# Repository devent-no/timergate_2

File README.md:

# timergate
PCB, 3D models, Firmware and software for timergates.

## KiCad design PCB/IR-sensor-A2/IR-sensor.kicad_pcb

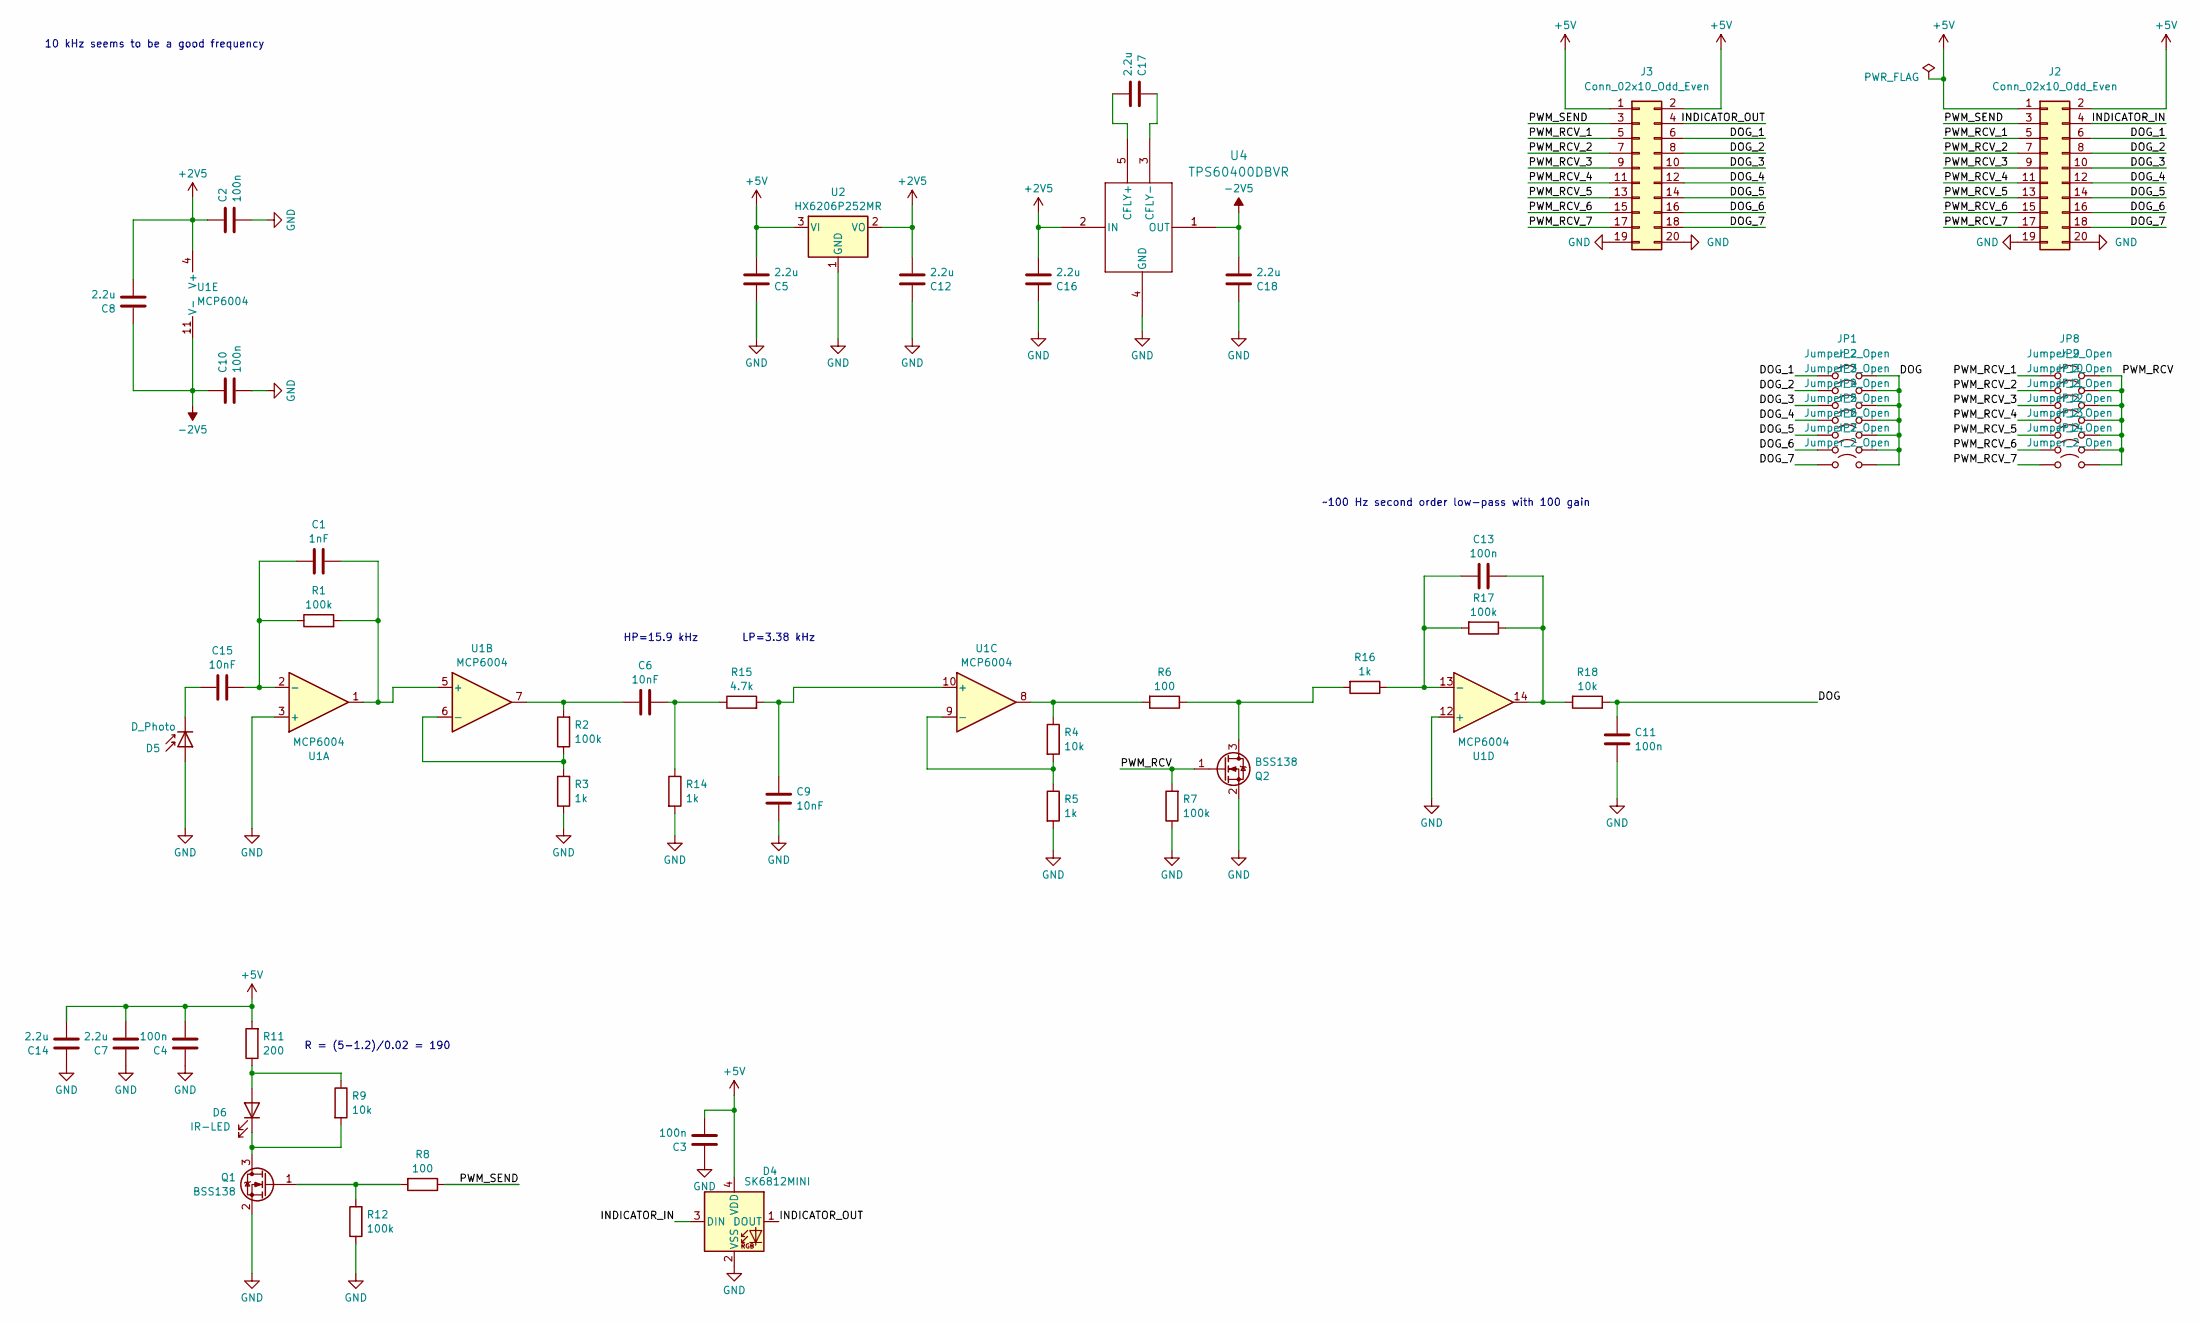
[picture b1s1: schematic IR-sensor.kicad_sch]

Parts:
C1: 1nF; C_0402_1005Metric; MPN CC0402KRX7R9BB102
C2, C3, C4, C10, C11, C13: 100n; C_0402_1005Metric; MPN CC0402KRX5R9BB104
C5, C7, C8, C12, C14, C16, C17, C18: 2.2u; C_0402_1005Metric; MPN CL05A225MQ5NSNC
C6, C9, C15: 10nF; C_0402_1005Metric; MPN CC0402KRX7R7BB103
D4: SK6812MINI; LED_SK6812MINI_PLCC4_3.5x3.5mm_P1.75mm; MPN SK6812mini
D5: D_Photo; LED_D5.0mm; MPN 1540051EC3590
D6: IR-LED; LED_D5.0mm; MPN VSLY5940
J2: Conn_02x10_Odd_Even; PinHeader_2x10_P1.27mm_Horizontal; MPN IPCP127M20PB28R
J3: Conn_02x10_Odd_Even; PinSocket_2x10_P1.27mm_Horizontal; MPN IPCP127F20PB28R
JP1, JP2, JP3, JP4, JP5, JP6, JP7, JP8, JP9, JP10, JP11, JP12, JP13, JP14: Jumper_2_Open; SolderJumper-2_P1.3mm_Open_Pad1.0x1.5mm
Q1, Q2: BSS138; SOT-23; MPN 4530-BSS138CT-ND
R1, R2, R7, R12, R17: 100k; R_0402_1005Metric; MPN RC0402FR-07100KL
R3, R5, R14, R16: 1k; R_0402_1005Metric; MPN 0402WGF1001TCE
R4, R9, R18: 10k; R_0402_1005Metric; MPN RC0402FR-0710KL
R6, R8: 100; R_0402_1005Metric; MPN RC0402FR-07100RL
R11: 200; R_0402_1005Metric; MPN 0402WGF2000TCE
R15: 4.7k; R_0402_1005Metric; MPN RC0402FR-074K7L
U1: MCP6004; SOIC-14_3.9x8.7mm_P1.27mm; MPN MCP6004T-I/SL
U2: HX6206P252MR; SOT-23-3; MPN HX6206P252MR
U4: TPS60400DBVR; SOT-23-5; MPN TPS60400DBVR

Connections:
+2V5: C2.2, C8.1, C12.2, C16.2, U1.4 (V+), U2.2 (VO), U4.2 (IN)
+5V: C3.1, C4.1, C5.2, C7.1, C14.1, D4.4 (VDD), J2.1, J2.2, J3.1, J3.2, R11.2, U2.3 (VI)
-2V5: C8.2, C10.2, C18.2, U1.11 (V-), U4.1 (OUT)
/DOG: C11.1, JP1.2 (B), JP2.2 (B), JP3.2 (B), JP4.2 (B), JP5.2 (B), JP6.2 (B), JP7.2 (B), R18.1
/DOG_1: J2.6, J3.6, JP1.1 (A)
/DOG_2: J2.8, J3.8, JP2.1 (A)
/DOG_3: J2.10, J3.10, JP3.1 (A)
/DOG_4: J2.12, J3.12, JP4.1 (A)
/DOG_5: J2.14, J3.14, JP5.1 (A)
/DOG_6: J2.16, J3.16, JP6.1 (A)
/DOG_7: J2.18, J3.18, JP7.1 (A)
/INDICATOR_IN: D4.3 (DIN), J2.4
/INDICATOR_OUT: D4.1 (DOUT), J3.4
/PWM_RCV: JP8.2 (B), JP9.2 (B), JP10.2 (B), JP11.2 (B), JP12.2 (B), JP13.2 (B), JP14.2 (B), Q2.1 (G), R7.2
/PWM_RCV_1: J2.5, J3.5, JP8.1 (A)
/PWM_RCV_2: J2.7, J3.7, JP9.1 (A)
/PWM_RCV_3: J2.9, J3.9, JP10.1 (A)
/PWM_RCV_4: J2.11, J3.11, JP11.1 (A)
/PWM_RCV_5: J2.13, J3.13, JP12.1 (A)
/PWM_RCV_6: J2.15, J3.15, JP13.1 (A)
/PWM_RCV_7: J2.17, J3.17, JP14.1 (A)
/PWM_SEND: J2.3, J3.3, R8.1
GND: C2.1, C3.2, C4.2, C5.1, C7.2, C9.2, C10.1, C11.2, C12.1, C14.2, C16.1, C18.1, D4.2 (VSS), D5.2 (A), J2.19, J2.20, J3.19, J3.20, Q1.2 (S), Q2.2 (S), R3.1, R5.2, R7.1, R12.1, R14.2, U1.3 (+), U1.12 (+), U2.1 (GND), U4.4 (GND)
unnamed: C6.1, R14.1, R15.1
unnamed: C6.2, R2.2, U1.7
unnamed: C13.1, R17.1, R18.2, U1.14
unnamed: C15.2, D5.1 (K)
unnamed: D6.2 (A), R9.1, R11.1
unnamed: D6.1 (K), Q1.3 (D), R9.2
unnamed: Q1.1 (G), R8.2, R12.2
unnamed: Q2.3 (D), R6.1, R16.2
unnamed: R4.1, R6.2, U1.8
unnamed: C1.1, C15.1, R1.1, U1.2 (-)
unnamed: C1.2, R1.2, U1.1, U1.5 (+)
unnamed: R2.1, R3.2, U1.6 (-)
unnamed: C9.1, R15.2, U1.10 (+)
unnamed: R4.2, R5.1, U1.9 (-)
unnamed: C13.2, R16.1, R17.2, U1.13 (-)
unnamed: C17.2, U4.5 (CFLY+)
unnamed: C17.1, U4.3 (CFLY-)

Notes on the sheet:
R = (5-1.2)/0.02 = 190
LP=3.38 kHz
10 kHz seems to be a good frequency
HP=15.9 kHz
~100 Hz second order low-pass with 100 gain

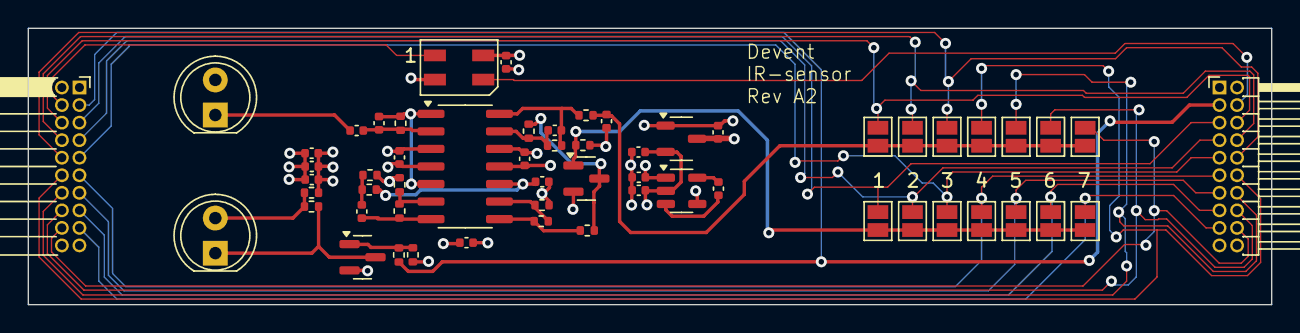
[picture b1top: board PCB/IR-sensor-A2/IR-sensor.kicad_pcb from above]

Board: 4 copper layers, 90.0 x 20.0 mm, 58 parts (0 on the bottom side), 40 nets.

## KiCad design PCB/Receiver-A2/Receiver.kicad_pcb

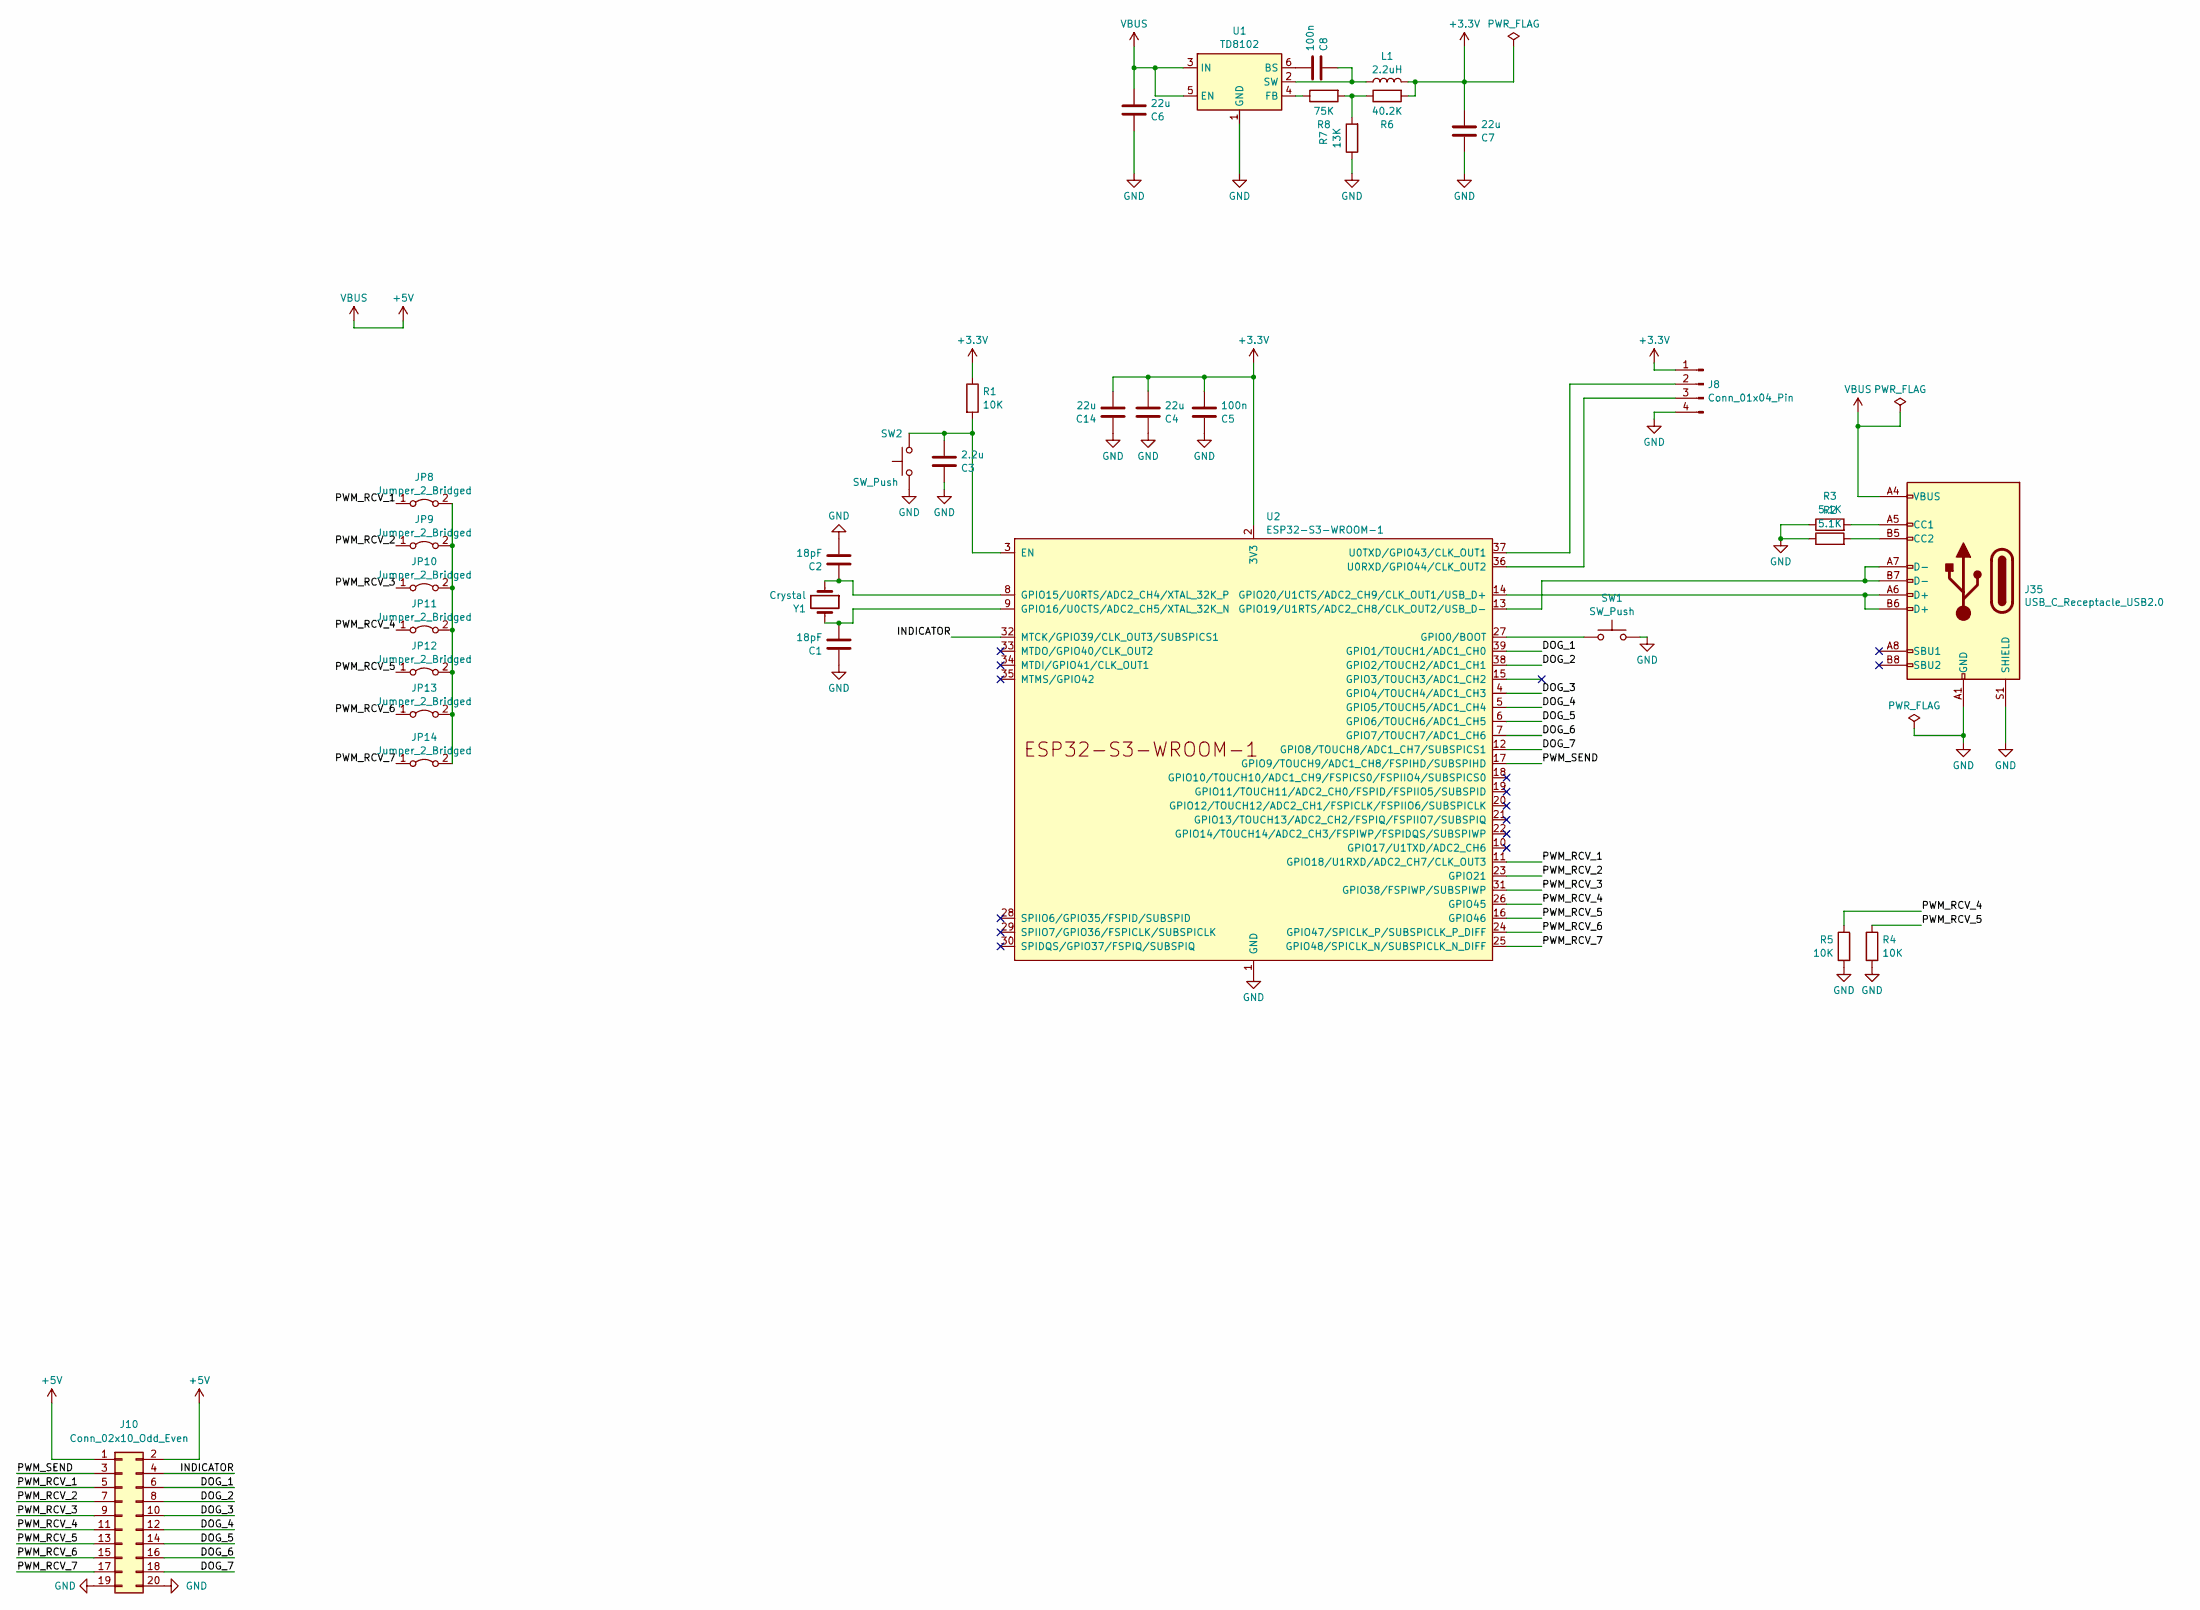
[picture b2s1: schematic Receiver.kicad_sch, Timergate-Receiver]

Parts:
C1, C2: 18pF; C_0402_1005Metric; MPN CC0402JRNPO9BN180
C3: 2.2u; C_0402_1005Metric; MPN CL05A225MQ5NSNC
C4, C6, C7, C14: 22u; C_0805_2012Metric; MPN CL21A226MPQNNNG
C5, C8: 100n; C_0402_1005Metric; MPN CC0402KRX5R9BB104
J8: Conn_01x04_Pin; PinHeader_1x04_P2.54mm_Vertical_SMD_Pin1Left
J10: Conn_02x10_Odd_Even; PinSocket_2x10_P1.27mm_Horizontal; MPN IPCP127F20PB28R
J35: USB_C_Receptacle_USB2.0; USB-C; MPN U262-161N-4BVC11
JP8, JP9, JP10, JP11, JP12, JP13, JP14: Jumper_2_Bridged; SolderJumper-2_P1.3mm_Bridged_Pad1.0x1.5mm
L1: 2.2uH; L_1008_2520Metric; MPN SLO252010T4R7MTT
R1, R4, R5: 10K; R_0402_1005Metric; MPN RC0402FR-0710KL
R2, R3: 5.1K; R_0402_1005Metric; MPN RC0402JR-075K1L
R6: 40.2K; R_0402_1005Metric; MPN RC0402FR-0739K2L
R7: 13K; R_0402_1005Metric; MPN RC0402JR-0713KL
R8: 75K; R_0402_1005Metric; MPN RC0402FR-0775KL
SW1, SW2: SW_Push; TSA343G0; MPN TSA343G00-250DZY
U1: TD8102; SOT-23-6; MPN TD8102
U2: ESP32-S3-WROOM-1; MPN ESP32-S3-WROOM-1U-N4R2
Y1: Crystal; Crystal_SMD_3215-2Pin_3.2x1.5mm; MPN Q13FC1350000400

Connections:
+3.3V: C4.2, C5.2, C7.2, C14.2, J8.1, L1.2, R1.1, R6.2, U2.2 (3V3)
+5V: C6.2, J10.1, J10.2, U1.3 (IN), U1.5 (EN); also elsewhere on the board
/DOG_1: J10.6, U2.39 (GPIO1/TOUCH1/ADC1_CH0)
/DOG_2: J10.8, U2.38 (GPIO2/TOUCH2/ADC1_CH1)
/DOG_3: J10.10, U2.4 (GPIO4/TOUCH4/ADC1_CH3)
/DOG_4: J10.12, U2.5 (GPIO5/TOUCH5/ADC1_CH4)
/DOG_5: J10.14, U2.6 (GPIO6/TOUCH6/ADC1_CH5)
/DOG_6: J10.16, U2.7 (GPIO7/TOUCH7/ADC1_CH6)
/DOG_7: J10.18, U2.12 (GPIO8/TOUCH8/ADC1_CH7/SUBSPICS1)
/INDICATOR: J10.4, U2.32 (MTCK/GPIO39/CLK_OUT3/SUBSPICS1)
/PWM_RCV_1: J10.5, JP8.1 (A), U2.11 (GPIO18/U1RXD/ADC2_CH7/CLK_OUT3)
/PWM_RCV_2: J10.7, JP9.1 (A), U2.23 (GPIO21)
/PWM_RCV_3: J10.9, JP10.1 (A), U2.31 (GPIO38/FSPIWP/SUBSPIWP)
/PWM_RCV_4: J10.11, JP11.1 (A), R5.1, U2.26 (GPIO45)
/PWM_RCV_5: J10.13, JP12.1 (A), R4.1, U2.16 (GPIO46)
/PWM_RCV_6: J10.15, JP13.1 (A), U2.24 (GPIO47/SPICLK_P/SUBSPICLK_P_DIFF)
/PWM_RCV_7: J10.17, JP14.1 (A), U2.25 (GPIO48/SPICLK_N/SUBSPICLK_N_DIFF)
/PWM_SEND: J10.3, U2.17 (GPIO9/TOUCH9/ADC1_CH8/FSPIHD/SUBSPIHD)
GND: C1.1, C2.2, C3.1, C4.1, C5.1, C6.1, C7.1, C14.1, J8.4, J10.19, J10.20, R2.1, R3.1, R4.2, R5.2, R7.1, SW1.2, SW2.1, U1.1 (GND), U2.1 (GND), U2.40 (GND), U2.41 (GND); also elsewhere on the board
unnamed 19: R3.2; also elsewhere on the board
unnamed 20: R2.2; also elsewhere on the board
unnamed: J8.2, U2.37 (U0TXD/GPIO43/CLK_OUT1)
unnamed: J8.3, U2.36 (U0RXD/GPIO44/CLK_OUT2)
unnamed: JP8.2 (B), JP9.2 (B), JP10.2 (B), JP11.2 (B), JP12.2 (B), JP13.2 (B), JP14.2 (B)
unnamed: R6.1, R7.2, R8.2
unnamed: C8.2, U1.6 (BS)
unnamed: R8.1, U1.4 (FB)
unnamed: C8.1, L1.1, U1.2 (SW)
unnamed: C3.2, R1.2, SW2.2, U2.3 (EN)
unnamed: SW1.1, U2.27 (GPIO0/BOOT)
unnamed: C2.1, U2.8 (GPIO15/U0RTS/ADC2_CH4/XTAL_32K_P), Y1.1
unnamed: C1.2, U2.9 (GPIO16/U0CTS/ADC2_CH5/XTAL_32K_N), Y1.2
unnamed 32: U2.13 (GPIO19/U1RTS/ADC2_CH8/CLK_OUT2/USB_D-); also elsewhere on the board
unnamed 33: U2.14 (GPIO20/U1CTS/ADC2_CH9/CLK_OUT1/USB_D+); also elsewhere on the board

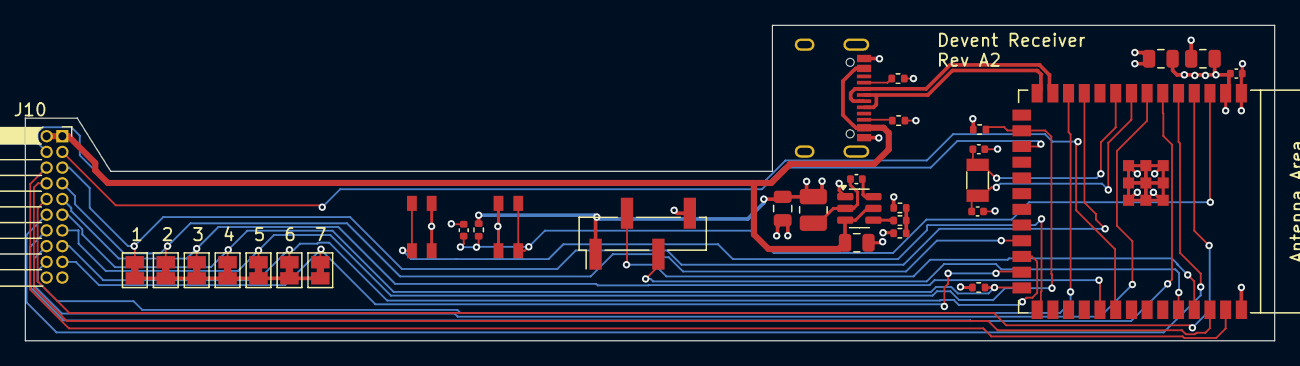
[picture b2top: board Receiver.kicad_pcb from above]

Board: 4 copper layers, 101.0 x 25.5 mm, 33 parts (0 on the bottom side), 34 nets.

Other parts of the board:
J6: USB_C_Receptacle_USB2.0; USB-C

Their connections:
+5V: J6.A4 (VBUS), J6.A9 (VBUS); also elsewhere on the board
GND: J6.A1 (GND), J6.A12 (GND), J6.S1 (SHIELD); also elsewhere on the board
unnamed 19: J6.A5 (CC1); also elsewhere on the board
unnamed 20: J6.B5 (CC2); also elsewhere on the board
unnamed 32: J6.A7 (D-), J6.B7 (D-); also elsewhere on the board
unnamed 33: J6.A6 (D+), J6.B6 (D+); also elsewhere on the board

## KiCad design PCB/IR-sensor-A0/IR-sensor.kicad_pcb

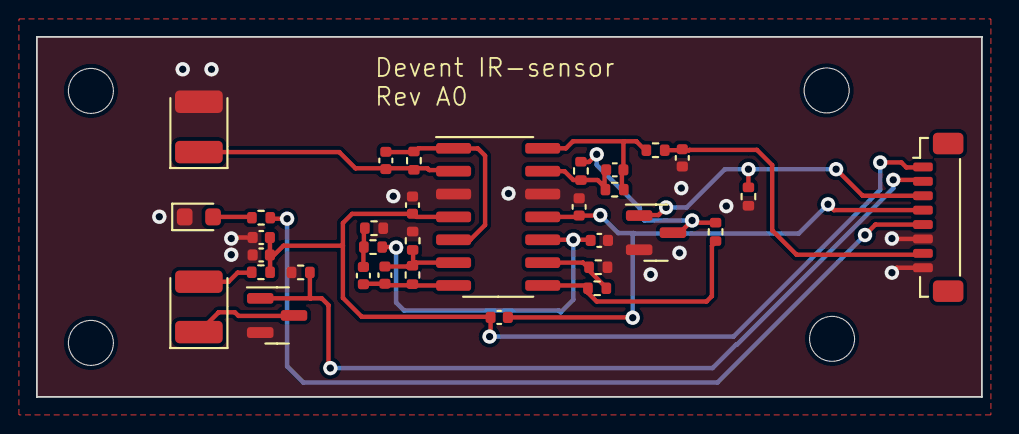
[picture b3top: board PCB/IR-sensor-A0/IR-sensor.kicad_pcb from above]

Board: 2 copper layers, 52.5 x 20.0 mm, 37 parts (0 on the bottom side), 21 nets.

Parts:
C1, C5: 10n; C_0402_1005Metric
C2, C3, C4, C6, C9, C10, C11, C13: 100n; C_0402_1005Metric
C7: 2.2u; C_0402_1005Metric
D1: IR-LED; LED_1210_3225Metric
D2: D_Photo; LED_1210_3225Metric
D3: LED; LED_0603_1608Metric
H1, H2, H3, H4: MountingHole; MountingHole_2.5mm
J1: Conn_01x06_Pin; JST_SUR_BM08B-SURS-TF_1x08-1MP_P0.80mm_Vertical
Q1, Q2: BSS138; SOT-23
R1, R2, R7, R12, R17: 100k; R_0402_1005Metric
R3, R5, R13, R14, R16: 1k; R_0402_1005Metric
R4, R18: 10k; R_0402_1005Metric
R6: 100; R_0402_1005Metric
R11: 27; R_0402_1005Metric
R15: 4.7k; R_0402_1005Metric
U1: MCP6004; SOIC-14_3.9x8.7mm_P1.27mm

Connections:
+2V5: C2.2, C3.1, C4.1, C7.1, J1.1, R11.2, U1.4 (V+)
-2V5: C3.2, C10.2, J1.4, U1.11 (V-)
/DOG: C11.1, J1.7, R18.1
/INDICATOR: J1.5, R13.2
/PWM_RCV: J1.3, Q2.1 (G), R7.2
/PWM_SEND: J1.2, Q1.1 (G), R12.2
GND: C2.1, C4.2, C7.2, C9.2, C10.1, C11.2, D2.2 (A), D3.1 (K), J1.6, J1.8, Q1.2 (S), Q2.2 (S), R3.1, R5.2, R7.1, R12.1, R14.2, U1.3 (+), U1.12 (+)
unnamed: C5.2, C6.2, R2.2, U1.7
unnamed: C6.1, R14.1, R15.1
unnamed: C13.1, R17.1, R18.2, U1.14
unnamed: D1.2 (A), R11.1
unnamed: D1.1 (K), Q1.3 (D)
unnamed: C1.1, D2.1 (K), R1.1, U1.2 (-)
unnamed: D3.2 (A), R13.1
unnamed: Q2.3 (D), R6.1, R16.2
unnamed: R4.1, R6.2, U1.8
unnamed: C1.2, R1.2, U1.1, U1.5 (+)
unnamed: C5.1, R2.1, R3.2, U1.6 (-)
unnamed: C9.1, R15.2, U1.10 (+)
unnamed: R4.2, R5.1, U1.9 (-)
unnamed: C13.2, R16.1, R17.2, U1.13 (-)

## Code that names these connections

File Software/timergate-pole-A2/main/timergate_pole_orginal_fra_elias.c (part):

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#define LEDC_MODE LEDC_LOW_SPEED_MODE
#define PWM_SEND_0 9
#define PWM_RCV_0 18
#define PWM_RCV_1 21
#define PWM_RCV_2 38
#define PWM_RCV_3 45
#define PWM_RCV_4 46
#define PWM_RCV_5 47
#define PWM_RCV_6 48
#define LEDC_DUTY_RES LEDC_TIMER_13_BIT // Set duty resolution to 13 bits
#define LEDC_DUTY (4095)                // Set duty to 50%. ((2 ** 13) - 1) * 50% = 4095
#define PWM_0_FREQUENCY (9000)          // Frequency in Hertz.
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uint8_t led_val[NUM_SENSORS] = {0};
uint8_t adc_channel[NUM_SENSORS] = {ADC_CHANNEL_0, ADC_CHANNEL_1, ADC_CHANNEL_3, ADC_CHANNEL_4, ADC_CHANNEL_5, ADC_CHANNEL_6, ADC_CHANNEL_7};
uint16_t break_limit[NUM_SENSORS] = {1000, 1000, 1000, 1000, 1000, 1000, 1000};
uint8_t rcv_gpios[NUM_SENSORS] = {PWM_RCV_0, PWM_RCV_1, PWM_RCV_2, PWM_RCV_3, PWM_RCV_4, PWM_RCV_5, PWM_RCV_6};
ledc_channel_t rcv_channels[NUM_SENSORS] = {LEDC_CHANNEL_1, LEDC_CHANNEL_2, LEDC_CHANNEL_3, LEDC_CHANNEL_4, LEDC_CHANNEL_5, LEDC_CHANNEL_6, LEDC_CHANNEL_7};
uint16_t offsets[NUM_SENSORS];
bool enabled[NUM_SENSORS] = {true, true, true, false, true, true, true};
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
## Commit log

2024-08-15 First commit of the pole firmware
2024-08-15 Added PCB and 3D models
2024-08-15 Minor clean ups
2024-08-15 Add option to sync time between poles. Right now sync is done via socket and hardcoded Posix timestamp, but should use ESPnow to 'commit' at the same time. Should also add option to use a timestamp e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
2024-08-15 Added the ap firmware
2024-08-15 Minor clean upås
2024-08-15 Remove build
2024-08-19 Add support for ESPnow, use separate queue for breaks.
2024-08-20 Central unit is now set up as an access point instead of connecting to local AP
2025-01-06 New PCB revision almost ready
2025-01-06 Adding the older go code base
2025-02-20 Rev A2 received, board bring-up on A2
2025-02-21 Added option to disable a sensor, since it can interfere with the testing.
2025-04-15 La til esp-now som vanlig mappe
2025-04-15 La til docs-mappe og oppdaterte .gitignore
2025-04-16 several minor changes in config and timergate_server.c, flash ok
2025-04-16 moved to esp-idf 5.1
2025-04-16 test, no chagnes
2025-04-16 Fjern backupfil fra git tracking
2025-04-16 Legg til backup-fil i .gitignore
2025-04-17 some changes to fix webSocet connection
2025-04-17 some more changes to fix gui connection
2025-04-18 no build-flash issuees, button actions without fault-indication
2025-04-18 before adjustment against original timergate_server.c and timergate_rest.c
2025-04-18 first version vhere gui and ap is playing together
2025-04-20 changed to direct uri to gui files
2025-04-20 added config.uri_match_fn = httpd_uri_match_wildcard and returne to hashed gui-config/files
2025-04-20 after removal of ws_broadcast_task
2025-04-20 added correct mac-adr. handeling of 2 poles
2025-04-21 gui expand, new user layout
2025-04-23 status before starting with break-logick
2025-04-23 added filteredbreak-logic
2025-04-24 added more logging for break-detection
2025-04-24 more logic for break-detection
2025-04-24 Corrected passering/split logic
2025-04-24 added documentation for passering/split concept
2025-04-28 more filtering before sending passage to gui
2025-05-06 changed to wifi channel 6
2025-05-08 Added timer-gui content
2025-05-12 timer-gui adjustments
2025-05-12 status-indicators defined in md doc
2025-05-13 improved startup time
2025-05-13 status-indcators.md updated
2025-05-13 LED optimalization
2025-05-13 higpoint search fixing
2025-05-13 higpoint search fixing finished
2025-05-13 adding variable for num of sencores to alert
2025-05-13 troubleshooting red alert with less than 7 senscors
2025-05-14 fixing missing wifi on startup
2025-05-14 more fixing missing wifi on startup
2025-05-14 before adding highpoint fine tuning
2025-05-16 Added support for IP/timergate.local gui config
2025-05-16 added automatic timesync when client is connected
2025-05-17 solving time jump issue
2025-05-18 adding device reset etc
2025-05-19 change of defaults and calibration optimalization
2025-05-20 change of defaults and calibration optimalization2
2025-05-20 pole, got lost, rolback to yesterdays version
2025-05-20 pole, more calibration fixes
2025-05-21 pole, rolback to 14.5.25
2025-05-23 pole, adding deepsleep
2025-05-23 pole, added soft, hard and factory reset again
2025-05-23 gui, filtering not connected poles
2025-05-25 Timer log layout
2025-05-25 Pole highpointsearch quality optimalization
2025-05-26 Pole, reduce frequency for K=0 messages
2025-05-27 server cleanup
2025-05-27 adding passage monitor
2025-05-28 fixing passage monitor
2025-05-30 improve passage detection, use pole times only
2025-05-30 Ignore .cache folders and local log files
2025-05-31 updated passage detection, using pole times only, more error fixing
2025-05-31 updated passage detection, backend finished
2025-06-01 updated passage detection pole and gui
2025-06-02 before start of ESP_NOW migration
2025-06-02 ESP_NOW migration phase 1 done
2025-06-02 ESP_NOW migration phase 2 - part 1 done
2025-06-03 ESP_NOW migration phase 2 - part 1 done buld fix
2025-06-03 ESP_NOW migration phase 2 completed, ready for phase 3
2025-06-03 ESP_NOW migration phase 3 completed
2025-06-03 ESP_NOW migration phase 4 completed
2025-06-04 ESP_NOW migration phase 5 completed
2025-06-04 ESP_NOW migration phase 6 - part 1 completed
2025-06-04 ESP_NOW migration phase 6 completed
2025-06-04 ESP_NOW migration phase 6 - bugfix
2025-06-04 ESP_NOW migration phase 6 - more bugfix
2025-06-06 ESP_NOW migration phase 6 - more bugfix rssi
2025-06-07 removed tcp from timergate-pole-a2
2025-06-07 ap improvements and removal of tcp to pole
2025-06-07 ap improvements and removal of tcp to pole- cleanup
2025-06-08 ap rssi fix
2025-06-08 pole led fix, removal of tcp-state
2025-06-09 pole fix for loss of AP, more...
2025-06-09 rolback to before fixing ap loss, got lost...
2025-06-09 pole, removal of tcp and esp_now timestync and tcp hsearch
2025-06-10 pole, code cleanup partly done
2025-06-10 pole, before refactoring to simple model
2025-06-11 pole, after refactoring, calibration need fix
2025-06-11 rolback, pole simlifiation destroyed calibration process
2025-06-11 Fase 0: Løsriv kalibrering fra TCP-avhengighet - SUKSESS
2025-06-11 Fase 3: TCP-system forenklet - SUKSESS
2025-06-11 🎉 TIMERGATE REFAKTORERING FULLFØRT - TOTAL SUKSESS
    Alle 4 faser gjennomført med perfekte resultater:
    FASE 0: ✅ Kalibrering løsrevet fra TCP-avhengighet
    FASE 1: ✅ WiFi reconnect system forenklet
    FASE 2: ✅ Status system redusert 8→4 statuser
    FASE 3: ✅ TCP system forenklet til minimal setup
    FASE 4: ✅ Ubrukt kode fjernet og ryddet
2025-06-11 Fjernet warnings på pole
2025-06-11 Reorganization for pole finalized, all good for now
2025-08-04 Oppdater .gitignore og fjern auto-genererte filer
2025-08-04 Implementer NVS-lagring og fiks passeringsdeteksjon
    - Legg til persistent lagring av passeringsparametere i NVS
    - Fiks hybrid timing-arkitektur for korrekt sequence-timeout
    - Aktiver process_break_for_passage_detection() kall
    - Legg til MAC-adresse i passeringslogging
    - Oppdater og reorganiser dokumentasjon
    - Oppdater komponent-avhengigheter
2025-08-05 Fikset gui slik at det benytter k4-meldingenes timestamp korrekt med mikrosekunder, fikset displayvisning til sekunder og 3 desimaler
2025-08-05 fikset gui stoppeklokke til å vise presis k4-tid
2025-08-19 Flere gui forbedringer, stolpestatus, klokkeformat og stopp/reset knapp
2025-08-20 Migrering fra A2 til A3, basisfunksjonalitet fungerer
2025-08-21 Migrering fra A2 til A3, noen mindre justeringer
2025-08-21 lag til forbedret logging av strøm og spenning på målestolpe
2025-08-22 power montioring fase 1 - målestolpe er implementert
